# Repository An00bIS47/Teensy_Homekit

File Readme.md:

# Homekit

This project uses [platformio](https://platformio.org) as build tool. 

In the root directory of the project is a file named `platformio.ini` where you can define building environments, dependent libraries, add flags for compiling etc.

The `platformio.ini` consists of multiple environments (boards or build configurations) and uses additional scripts for modifying parameters for building depending on the users choices.

In short the command to build and upload this would be:

`pio run -e teensy_41 -t upload` 

or

`pio run -e teensy_41_debug -t upload` 

depending on the enviroment you want to build. Leave out `-t upload` for compiling only.

## plugins option:
```
[plugins]
bme280 = 1
led = 1
dht = 0
hygrometer = 0
knx = 0
```

With this option you can choose, which plugin should be available and enabled for your build. You can select multiple.
A `extra_script` will add the required source files to the `src_filter` and will also add the required defines and include paths.

## custom_options:

For each environment you will find the `custom_options`. There you can define, which feature options should be available. 

```
custom_options =
    teensy_debug = 0
    teensy_config_spiffs_ext = 0
    teensy_config_spiffs_int = 0
    config_eeprom = 1
    qrcode = 1
    ntp = 1
    webserver = 0
    ota_update = 0
    keystore = 0
    reset = 1
    wifi = 0
```

For the Teensy, only `teensy_debug`, `config_eeprom`, `ntp`, `qr_code` and `reset` will be working right now.

### teensy_debug
This will enable TeensyDebug

### config_eeprom
Use EEPROM to save the configuration and pairings

### ntp
Enables NTP as Time source

### reset
This will reset and delete the configuration from EEPROM.

### qr_code
This will enable a QR code generation and will print the QR code for pairing to Serial

## extra_scripts:

The scripts are located in the `scripts/platformio` folder and are referenced in the platformio.ini under 

```
[common]
extra_scripts =
	pre:scripts/platformio/pre_increment_version.py
	pre:scripts/platformio/pre_config_builder.py
	pre:scripts/platformio/pre_debug_macro.py
	;post:scripts/platformio/post_custom_debug_flags.py
	post:scripts/platformio/post_upload_delay.py
        scripts/platformio/custom_targets.py
```

The scripts do the following:
* `pre:scripts/platformio/pre_increment_version.py`:
 Increments the build number in the file `HAPBuildnumber` and adds infos about the git repository to `HAPVersionHomekit`
* `pre:scripts/platformio/pre_config_builder.py`: 
 Adds build flags (in particular: src_filter and build_flags) depending on the choices of the field `custom_options` for each environment. Additional it adds the same build flags for each "selected" plugin
* `pre:scripts/platformio/pre_debug_macro.py`: 
  Basically just adds the define `DEBUG=1` if the `release_type` is `debug`
* `post:scripts/platformio/post_custom_debug_flags.py`:
  This would change the `-0g`optimization parameter (which adds platformio as default if the `release_type` is set to `debug`) to `-0s`. Currently this is commented out
* `post:scripts/platformio/post_upload_delay.py`: 
  Adds a small delay of a few seconds after compiling so that the serial monitor can find the Teensy on the USB port.
* `scripts/platformio/custom_targets.py`: 
  Adds additional targets to the `pio run` command, like `teensy_size`, `tycmd reset` and so on.

I have not tested the scripts with Windows, but they should work on macOS and Linux.

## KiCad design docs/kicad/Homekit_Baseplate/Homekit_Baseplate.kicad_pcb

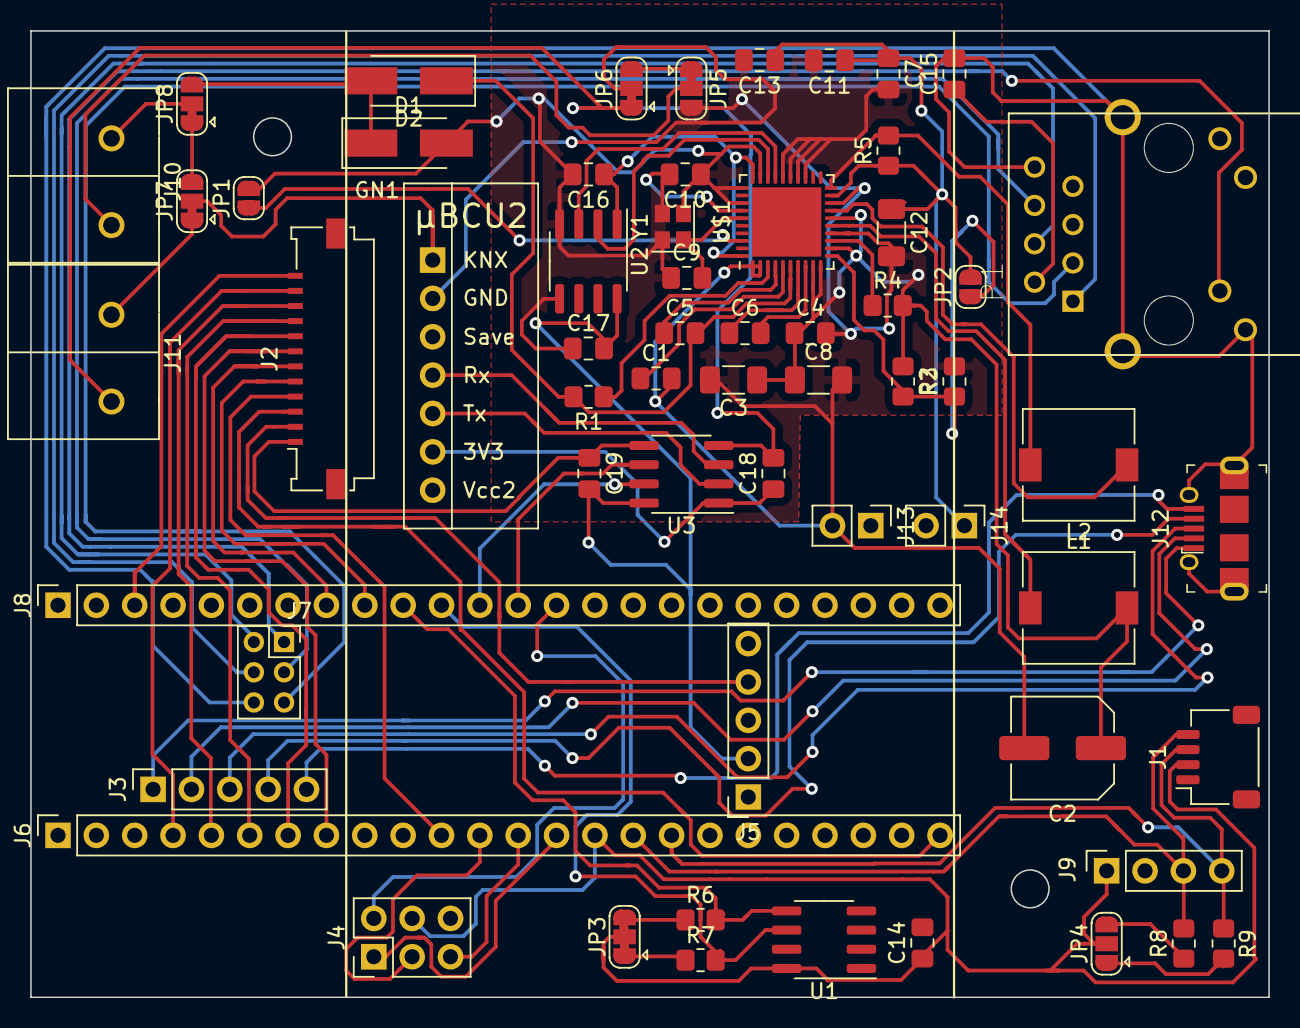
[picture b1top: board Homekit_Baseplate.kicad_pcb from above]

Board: 2 copper layers, 82.0 x 64.0 mm, 61 parts (0 on the bottom side), 68 nets.

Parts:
C1: 100nF / 50V; C_0805_2012Metric_Pad1.18x1.45mm_HandSolder
C2: 100µF / 35V; C_Elec_6.3x7.7
C3: 1µF / 50V; C_1206_3216Metric_Pad1.33x1.80mm_HandSolder
C4, C11: 10µF / 6.3V; C_0805_2012Metric_Pad1.18x1.45mm_HandSolder
C5: 47nF / 50V; C_0805_2012Metric_Pad1.18x1.45mm_HandSolder
C6: 47nF / 25V; C_0805_2012Metric_Pad1.18x1.45mm_HandSolder
C7, C13, C16, C17, C18, C19: 100nF / 6.3V; C_0805_2012Metric_Pad1.18x1.45mm_HandSolder
C8, C12: 10µF / 6.3V; C_1206_3216Metric_Pad1.33x1.80mm_HandSolder
C9, C10: 9pF / 6.3V; C_0805_2012Metric_Pad1.18x1.45mm_HandSolder
C14: 0.1µF / 6.3V; C_0805_2012Metric_Pad1.18x1.45mm_HandSolder
C15: 0.1µF / 50V; C_0805_2012Metric_Pad1.18x1.45mm_HandSolder
D1: TVS SMA40; D_SMA_Handsoldering
D2: D1; D_SMA_Handsoldering
GN1: Konnekting_µBCU; MicroBCU2_Solderd_Vertical
J1: J I2C/Serial QWIIC; JST_SH_SM04B-SRSS-TB_1x04-1MP_P1.00mm_Horizontal
J2: J Faceplate Connector; Molex_200528-0120_1x12-1MP_P1.00mm_Horizontal
J3: Teensy 4.1 USB; PinSocket_1x05_P2.54mm_Vertical
J4: SPI Breakout; PinHeader_2x03_P2.54mm_Vertical
J5: Teensy 4.1 Extra; PinSocket_1x05_P2.54mm_Vertical
J6: Teensy 4.1 Left; PinSocket_1x24_P2.54mm_Vertical
J7: Teensy 4.1 Ethernet Breakout; PinSocket_2x03_P2.00mm_Vertical
J8: Teensy 4.1 Right; PinSocket_1x24_P2.54mm_Vertical
J9: J I2C/Serial; PinSocket_1x04_P2.54mm_Vertical
J10, J11: Wago_243-211; WAGO 243-211 KNX
J12: Micro USB; USB_Micro_AB_Female_0475890001
J13, J14: 5V KNX Out; PinHeader_1x02_P2.54mm_Vertical
JP1: SJ HIGH POWER; SolderJumper-2_P1.3mm_Open_RoundedPad1.0x1.5mm
JP2: SJ 3V3 ONLY; SolderJumper-2_P1.3mm_Open_RoundedPad1.0x1.5mm
JP3: SJ ATECC608A PULLUPS; SolderJumper-3_P1.3mm_Bridged123_RoundedPad1.0x1.5mm
JP4: SJ QWIIC PULLUPS; SolderJumper-3_P1.3mm_Open_RoundedPad1.0x1.5mm
JP5, JP6, JP7, JP8: JUMPER-SMT_3_1-NC; SolderJumper-3_P1.3mm_Bridged12_RoundedPad1.0x1.5mm
L1, L2: 220µH; L_7.3x7.3_H4.5
P1: J1B1211CCD
R1: 22R; R_0805_2012Metric_Pad1.20x1.40mm_HandSolder
R2: 33k; R_0805_2012Metric_Pad1.20x1.40mm_HandSolder
R3: 180k; R_0805_2012Metric_Pad1.20x1.40mm_HandSolder
R4, R5: 1R; R_0805_2012Metric_Pad1.20x1.40mm_HandSolder
R6, R7, R8, R9: 4k7; R_0805_2012Metric_Pad1.20x1.40mm_HandSolder
U1: ATECC608A; SOIC-8_3.9x4.9mm_P1.27mm
U2, U3: ADuM1201AR; SOIC-8_3.9x4.9mm_P1.27mm
U$1: NCN5120; QFN-40-1EP_6x6mm_P0.5mm_EP4.6x4.6mm
Y1: 16MHz; Crystal_SMD_2520-4Pin_2.5x2.0mm

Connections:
+3V3: C14.1, C17.2, C19.2, J1.2, J2.12, J4.4, J5.2, J6.15, J8.3, J9.1, JP3.2, JP4.2, U1.8, U2.8, U3.8
+5V: J3.1, J8.1, J12.1
/CS_0: J4.3, J6.12
/Homekit_KNX/3V3_KNX_2: C18.1, GN1.6, U3.1
/Homekit_KNX/KNX+: J10.1, JP8.2
/Homekit_KNX/KNX-: J10.2, JP5.2
/Homekit_KNX/KNX_2+: J11.1, JP7.1
/Homekit_KNX/KNX_2-: C18.2, J11.2, JP6.1, U3.4
/Homekit_KNX/RX_1_KNX: U2.3, U$1.27
/Homekit_KNX/RX_2_KNX_2: GN1.4, U3.3
/Homekit_KNX/TX_1_KNX: U2.2, U$1.28
/Homekit_KNX/TX_2_KNX_2: GN1.5, U3.2
/LED_CONN: J2.9, J6.6
/LED_ERROR: J2.8, J6.7
/LED_ON: J2.11, J6.4
/LED_PROG: J2.10, J6.5
/LED_T41_PROG: J2.7, J6.8
/MISO_0: J4.1, J6.14
/MOSI_0: J4.5, J6.13
/PUSH_PROG: J2.4, J6.11
/PUSH_RESET: J2.3, J6.24
/PUSH_T41_PROG: J2.2, J5.4
/RX_1: J6.2, U2.7
/RX_3: J8.12, U3.7
/SCK_0: J4.2, J8.14
/SCL_0: J2.6, J8.8
/SCL_1: J8.11, R7.2, U1.6
/SCL_2_TX_6: J1.4, J6.16, J9.3, R8.2
/SDA_0: J2.5, J8.9
/SDA_1: J8.10, R6.2, U1.5
/SDA_2_RX_6: J1.3, J6.17, J9.4, R9.2
/TX_1: J6.3, U2.6
/TX_3: J8.13, U3.6
GND: C14.2, C15.2, C17.1, C19.1, J1.1, J2.1, J3.4, J3.5, J4.6, J5.3, J6.1, J7.5, J8.2, J8.15, J9.2, J12.4, J12.5, J12.SH, P1.8, P1.9, P1.13, P1.14, U1.4, U2.5, U3.5
GND1: C1.2, C2.2, C3.2, C4.2, C7.2, C8.2, C9.1, C10.1, C11.2, C12.2, C13.2, C16.2, D1.2, J13.2, J14.2, JP1.2, JP5.3, R3.2, U2.4, U$1.1, U$1.2, U$1.14, U$1.18, U$1.23, U$1.24, U$1.25, U$1.26, U$1.29, U$1.31, U$1.33, Y1.2, Y1.4
unnamed: C1.1, U$1.5
unnamed: C5.1, U$1.4
unnamed: C5.2, D2.1, R1.2, U$1.6
unnamed: C6.1, U$1.7
unnamed: C6.2, U$1.8
unnamed: C9.2, U$1.35, Y1.1
unnamed: C10.2, U$1.34, Y1.3
unnamed: C15.1, P1.2
unnamed: D1.1, D2.2, JP8.3
unnamed: GN1.1, JP7.2
unnamed: GN1.2, JP6.2
unnamed: J7.1, P1.4
unnamed: J7.2, P1.10
unnamed: J7.3, P1.1
unnamed: J7.4, P1.6
unnamed: J7.6, P1.3
unnamed: J3.2, J12.2
unnamed: J3.3, J12.3
unnamed: JP1.1, U$1.38
unnamed: JP2.1, R2.2, R3.1, U$1.11
unnamed: JP3.1, R7.1
unnamed: JP3.3, R6.1
unnamed: JP4.1, R9.1
unnamed: JP4.3, R8.1
unnamed: JP5.1, JP6.3
unnamed: JP7.3, JP8.1
unnamed: L1.1, U$1.15
unnamed: L2.1, U$1.17
unnamed: L2.2, R5.2, U$1.20
unnamed: R1.1, U$1.3
unnamed: R4.1, U$1.13
VCC_1: C7.1, C11.1, C12.1, C13.1, C16.1, J14.1, JP2.2, R5.1, U2.1, U$1.19, U$1.30, U$1.40
VCC_2: C2.1, C3.1, C4.1, C8.1, J13.1, L1.2, R2.1, R4.2, U$1.9, U$1.10, U$1.12, U$1.16

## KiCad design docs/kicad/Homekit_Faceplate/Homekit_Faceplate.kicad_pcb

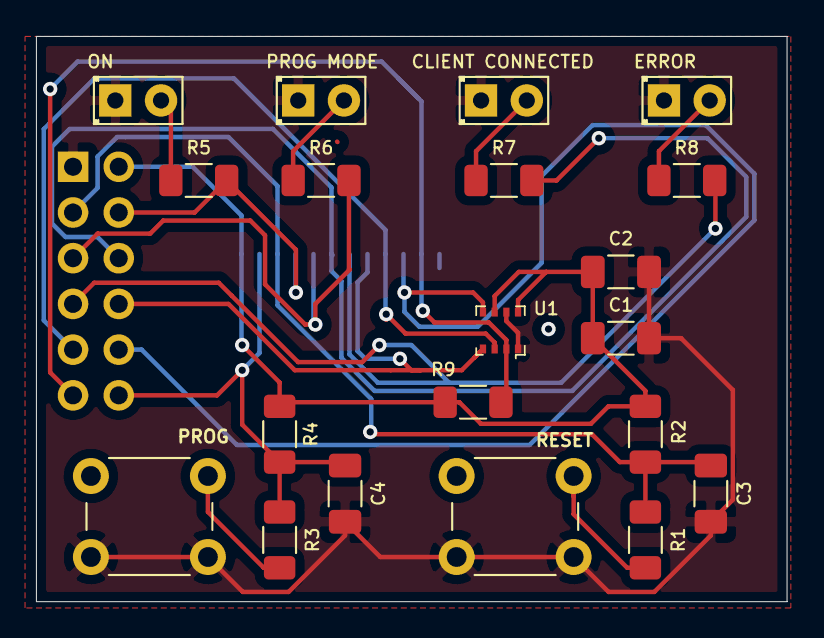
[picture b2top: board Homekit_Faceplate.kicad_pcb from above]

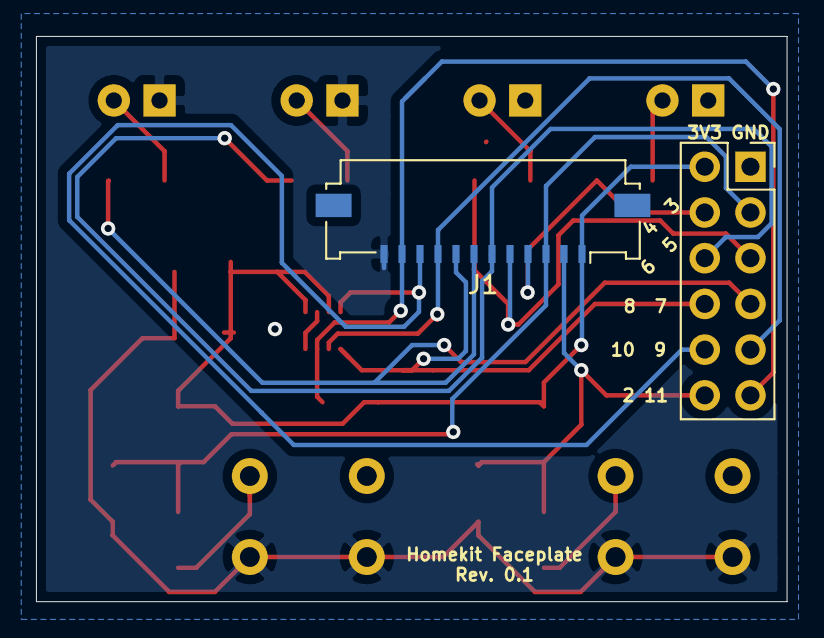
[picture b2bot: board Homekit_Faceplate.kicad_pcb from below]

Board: 2 copper layers, 41.7 x 31.4 mm, 22 parts (2 on the bottom side), 18 nets.

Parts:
C1, C2: 100nF; C_1206_3216Metric_Pad1.33x1.80mm_HandSolder
C3, C4: 0.1µF; C_1206_3216Metric_Pad1.33x1.80mm_HandSolder
D1: LED GREEN; LED_D2.0mm_W4.8mm_H2.5mm_FlatTop
D2, D4: LED RED; LED_D2.0mm_W4.8mm_H2.5mm_FlatTop
D3: LED ORANGE; LED_D2.0mm_W4.8mm_H2.5mm_FlatTop
J1: Conn_01x12; Molex_200528-0120_1x12-1MP_P1.00mm_Horizontal
J2: Conn_02x06_Odd_Even; PinSocket_2x06_P2.54mm_Vertical
R1, R3: 1k; R_1206_3216Metric_Pad1.30x1.75mm_HandSolder
R2, R4: 10k; R_1206_3216Metric_Pad1.30x1.75mm_HandSolder
R5, R6, R7, R8: 220R; R_1206_3216Metric_Pad1.30x1.75mm_HandSolder
R9: 4k7; R_1206_3216Metric_Pad1.30x1.75mm_HandSolder
SW1: PROG MODE; SW_PUSH_6mm
SW2: RESET; SW_PUSH_6mm
U1: BME280; Pressure_Sensor_LGA-8_2.5x2.5mm_BME280

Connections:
+3V3: C1.1, C2.1, J1.1, J2.2, R2.2, R4.2, R9.1, U1.6, U1.8
/2: C4.1, J1.2, J2.12, R3.1, R4.1
/3: C3.1, J1.3, J2.3, R1.1, R2.1
/4: J1.4, J2.4, R5.2
/5: J1.5, J2.5, R6.2
/6: J1.6, J2.6, R7.2
/7: J1.7, J2.7, R8.2
/8: J1.8, J2.8, U1.4
/9: J1.9, J2.9, U1.3
/10: J1.10, J2.10, U1.5
/11: J1.11, J2.11, R9.2, U1.2
GND: C1.2, C2.2, C3.2, C4.2, D1.1, D2.1, D3.1, D4.1, J1.12, J2.1, SW1.1, SW2.1, U1.1, U1.7
unnamed: D1.2, R5.1
unnamed: D2.2, R6.1
unnamed: D3.2, R7.1
unnamed: D4.2, R8.1
unnamed: R1.2, SW2.2
unnamed: R3.2, SW1.2

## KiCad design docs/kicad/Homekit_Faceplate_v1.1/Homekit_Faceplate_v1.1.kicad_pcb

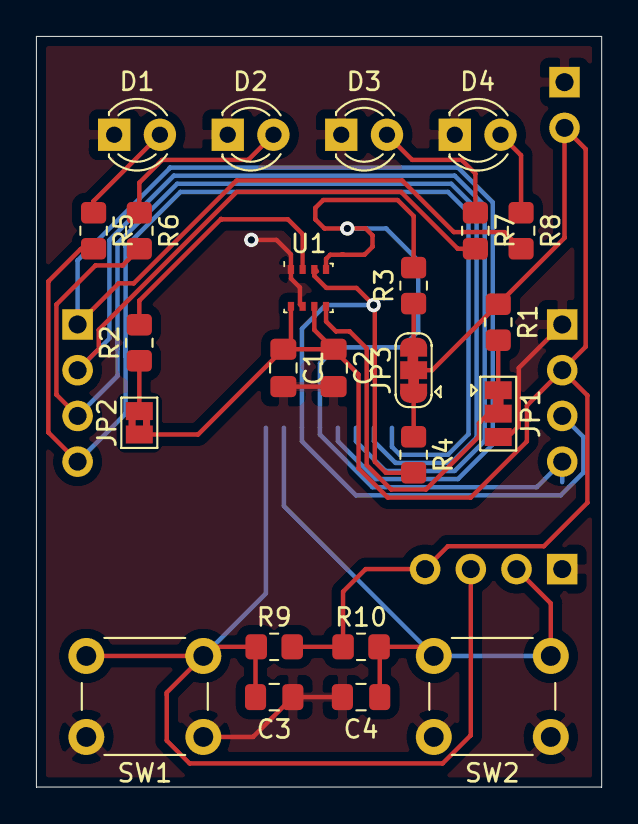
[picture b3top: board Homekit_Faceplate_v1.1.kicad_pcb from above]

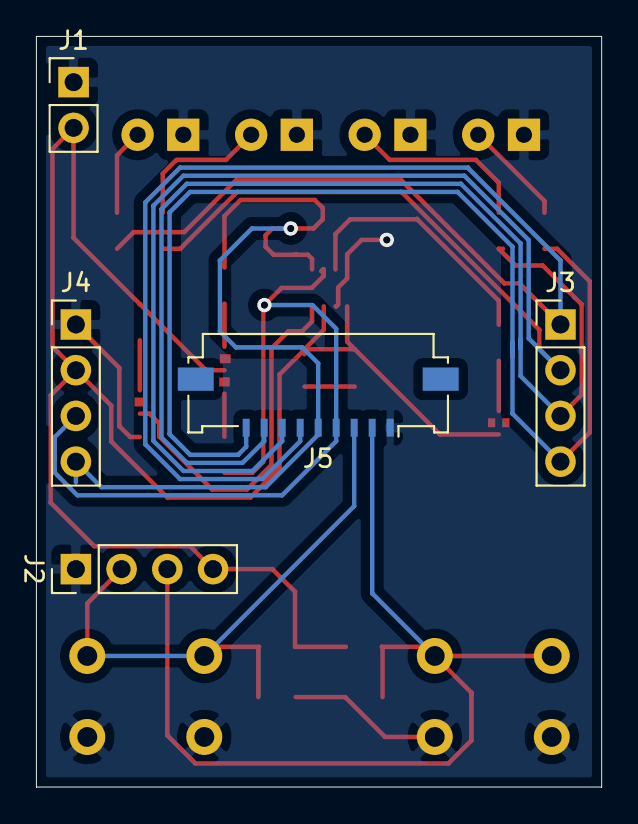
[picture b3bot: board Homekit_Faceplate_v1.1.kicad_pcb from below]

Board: 2 copper layers, 31.4 x 41.7 mm, 29 parts (5 on the bottom side), 20 nets.

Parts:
C1, C2, C3, C4: 0.1µF; C_0805_2012Metric_Pad1.18x1.45mm_HandSolder
D1: LED GREEN; LED_D3.0mm
D2, D4: LED RED; LED_D3.0mm
D3: LED ORANGE; LED_D3.0mm
J1: J Power; PinHeader_1x02_P2.54mm_Vertical
J2: J Push Buttons; PinHeader_1x04_P2.54mm_Vertical
J3: J Status LEDs; PinHeader_1x04_P2.54mm_Vertical
J4: J I2C; PinHeader_1x04_P2.54mm_Vertical
J5: J Flex Jumper to Teensy; Molex_200528-0090_1x09-1MP_P1.00mm_Horizontal
JP1: EN ADR PULLUP; SolderJumper-3_P1.3mm_Bridged12_Pad1.0x1.5mm
JP2: EN I2C MODE; SolderJumper-2_P1.3mm_Bridged2Bar_Pad1.0x1.5mm
JP3: EN I2C PULLUP; SolderJumper-3_P1.3mm_Bridged123_RoundedPad1.0x1.5mm
R1, R2, R3, R4: 4k7; R_0805_2012Metric_Pad1.20x1.40mm_HandSolder
R5, R6, R7, R8: 220R; R_0805_2012Metric_Pad1.20x1.40mm_HandSolder
R9, R10: 1k; R_0805_2012Metric_Pad1.20x1.40mm_HandSolder
SW1: SW PROG MODE; SW_PUSH_6mm
SW2: SW RESET; SW_PUSH_6mm
U1: BME280; Bosch_LGA-8_2.5x2.5mm_P0.65mm_ClockwisePinNumbering

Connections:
+3V3: C1.1, C2.1, J1.2, J2.4, J4.2, JP2.1, JP3.2, R1.1, R9.1, R10.1, U1.6, U1.8
/3: J3.4, J5.9, R5.2
/6: J3.3, J5.8, R6.2
/9: J3.2, J5.7, R7.2
/11: J3.1, J5.6, R8.2
/PB1: C3.1, J2.3, J5.2, R9.2, SW1.2
/PB2: C4.1, J2.2, J5.3, R10.2, SW2.2
/SCL: J4.4, J5.5, R3.2, U1.4
/SDA: J4.3, J5.4, R4.2, U1.3
GND: C1.2, C2.2, C3.2, C4.2, D1.1, D2.1, D3.1, D4.1, J1.1, J2.1, J4.1, J5.1, JP1.3, SW1.1, SW2.1, U1.1, U1.7
unnamed: D1.2, R5.1
unnamed: D2.2, R6.1
unnamed: D3.2, R7.1
unnamed: D4.2, R8.1
unnamed: JP1.1, R1.2
unnamed: JP1.2, U1.5
unnamed: JP2.2, R2.1
unnamed: JP3.1, R4.1
unnamed: JP3.3, R3.1
unnamed: R2.2, U1.2

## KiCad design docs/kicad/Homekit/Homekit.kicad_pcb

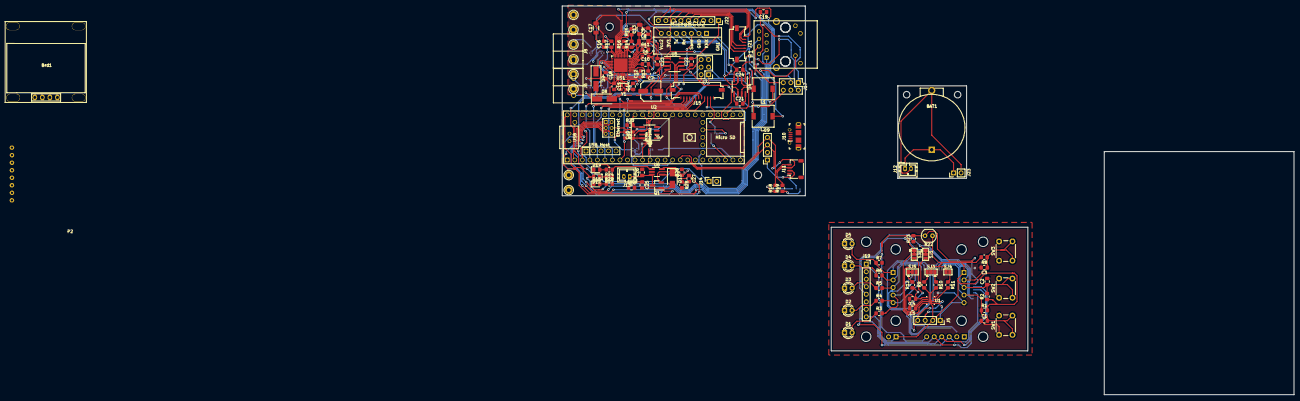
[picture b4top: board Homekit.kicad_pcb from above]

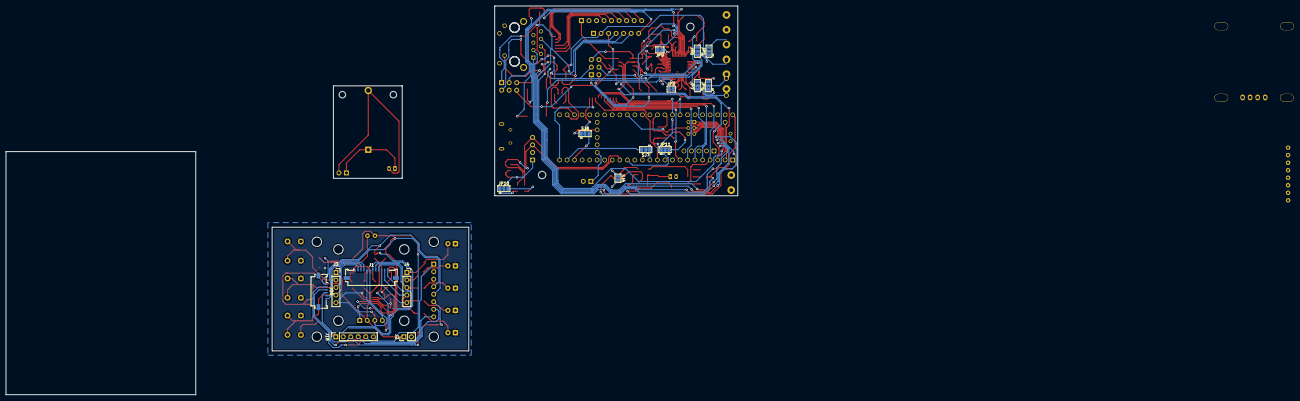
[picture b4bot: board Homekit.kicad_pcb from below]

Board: 2 copper layers, 246.8 x 131.1 mm, 124 parts (17 on the bottom side), 102 nets.

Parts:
BAT1: RTC Battery; Battery_Holder_Coin_2032_BS-7
Brd1: SSD1306; 128x64OLED
C1, C2, C3, C4, C5: 0.1µF; C_0805_2012Metric_Pad1.18x1.45mm_HandSolder
C6: 100nF / 50V; C_0805_2012Metric_Pad1.18x1.45mm_HandSolder
C7: 100µF / 35V; C_Elec_6.3x7.7
C8: 1µF / 50V; C_1206_3216Metric_Pad1.33x1.80mm_HandSolder
C9, C16: 10µF / 6.3V; C_0805_2012Metric_Pad1.18x1.45mm_HandSolder
C10: 47nF / 50V; C_0805_2012Metric_Pad1.18x1.45mm_HandSolder
C11: 47nF / 25V; C_0805_2012Metric_Pad1.18x1.45mm_HandSolder
C12, C18, C21, C22, C23, C24: 100nF / 6.3V; C_0805_2012Metric_Pad1.18x1.45mm_HandSolder
C13, C17: 10µF / 6.3V; C_1206_3216Metric_Pad1.33x1.80mm_HandSolder
C14, C15: 9pF / 6.3V; C_0805_2012Metric_Pad1.18x1.45mm_HandSolder
C19: 0.1µF / 50V; C_0805_2012Metric_Pad1.18x1.45mm_HandSolder
C20: 0.1µF / 6.3V; C_0805_2012Metric_Pad1.18x1.45mm_HandSolder
C25, C26: 4.7µF / 6.3 V; C_0805_2012Metric_Pad1.18x1.45mm_HandSolder
C27: 1µF / 6.3 V; C_0805_2012Metric_Pad1.18x1.45mm_HandSolder
D1: LED GREEN; LED_D3.0mm
D2, D4, D5: LED RED; LED_D3.0mm
D3: LED ORANGE; LED_D3.0mm
D8: TVS SMA40; D_SMA_Handsoldering
D9: D1; D_SMA_Handsoldering
D12: LED Red; LED_0805_2012Metric_Pad1.15x1.40mm_HandSolder
D13: B130-E3; D_SMA
D14: LED Green; LED_0805_2012Metric_Pad1.15x1.40mm_HandSolder
D15: LED RED; LED_0805_2012Metric_Pad1.15x1.40mm_HandSolder
GN1: Konnekting_µBCU; MicroBCU2_Solderd_Vertical
J1, J15: J Faceplate Connector; Molex_200528-0120_1x12-1MP_P1.00mm_Horizontal
J2: J Power; PinHeader_1x02_P2.54mm_Vertical
J3: J Push Buttons; PinSocket_1x05_P2.54mm_Vertical
J4: J Status LEDs; PinSocket_1x05_P2.54mm_Vertical
J5: J Display SSD1306; PinSocket_1x04_P2.54mm_Vertical
J6, J8: Wago_243-211; WAGO 243-211 KNX
J7: J KNX1 Breakout; PinHeader_2x03_P2.54mm_Vertical
J9: J I2C/Serial; PinSocket_1x04_P2.54mm_Vertical
J10: Micro USB; USB_Micro_AB_Female_0475890001
J11: J I2C/Serial QWIIC; JST_SH_SM04B-SRSS-TB_1x04-1MP_P1.00mm_Horizontal
J12: J RTC BatteryPack; JST_PH_B2B-PH-K_1x02_P2.00mm_Vertical
J13: JST Battery; JST_PH_B2B-PH-K_1x02_P2.00mm_Vertical
J14: J RTC Battery Socket; PinSocket_1x02_P2.54mm_Vertical
J17: J KNX2 Breakout; PinHeader_2x03_P2.54mm_Vertical
J18: J Breakout SPI; PinSocket_1x06_P2.54mm_Vertical
J19: J Display SSD1327; PinSocket_1x08_P2.54mm_Vertical
J20: J Connector SPI; Molex_200528-0060_1x06-1MP_P1.00mm_Horizontal
J21: J Connector SPI+; Molex_200528-0060_1x06-1MP_P1.00mm_Horizontal
J22: J SPI Display Breakout; PinSocket_1x09_P2.54mm_Vertical
J23: J RTC Breakout; PinHeader_1x02_P2.54mm_Vertical
JP4: SJ KNX1 GND; SolderJumper-3_P1.3mm_Bridged2Bar12_Pad1.0x1.5mm
JP5: SJ KNX2 GND; SolderJumper-3_P1.3mm_Bridged2Bar12_Pad1.0x1.5mm
JP6: SJ KNX2+; SolderJumper-3_P1.3mm_Bridged2Bar12_Pad1.0x1.5mm
JP7: SJ KNX1+; SolderJumper-3_P1.3mm_Bridged2Bar12_Pad1.0x1.5mm
JP8: SJ HIGH POWER; SolderJumper-2_P1.3mm_Open_Pad1.0x1.5mm
JP9: SJ 3V3 ONLY; SolderJumper-2_P1.3mm_Open_Pad1.0x1.5mm
JP10: SJ QWIIC PULLUPS; SolderJumper-3_P1.3mm_Open_Pad1.0x1.5mm
JP11: SJ ATECC608A PULLUPS; SolderJumper-3_P1.3mm_Bridged2Bar123_Pad1.0x1.5mm
L1, L2: 220µH; L_7.3x7.3_H4.5
P1: J1B1211CCD
P2: SSD1327; Waveshare_OLED_SSD1327_128x128
Q1: DMP1045U; SOT-23_Handsoldering
R1, R2, R8: 1k; R_0805_2012Metric_Pad1.20x1.40mm_HandSolder
R3, R4, R5, R6, R7, R29: 220R; R_0805_2012Metric_Pad1.20x1.40mm_HandSolder
R9, R10, R11, R12, R18, R19, R20, R21: 4k7; R_0805_2012Metric_Pad1.20x1.40mm_HandSolder
R13: 22R; R_0805_2012Metric_Pad1.20x1.40mm_HandSolder
R14: 33k; R_0805_2012Metric_Pad1.20x1.40mm_HandSolder
R15: 180k; R_0805_2012Metric_Pad1.20x1.40mm_HandSolder
R16, R17: 1R; R_0805_2012Metric_Pad1.20x1.40mm_HandSolder
R22: R_PHOTO; R_LDR_4.9x4.2mm_P2.54mm_Vertical
R23, R25: 10k; R_0805_2012Metric_Pad1.20x1.40mm_HandSolder
R24, R27: 470R; R_0805_2012Metric_Pad1.20x1.40mm_HandSolder
R26: 100k; R_0805_2012Metric_Pad1.20x1.40mm_HandSolder
R28: 2k5; R_0805_2012Metric_Pad1.20x1.40mm_HandSolder
SJ1, SJ2: SolderJumper_3_Bridged12; SolderJumper-3_P1.3mm_Bridged12_Pad1.0x1.5mm
SJ3: EN I2C PULLUP; SolderJumper-3_P1.3mm_Bridged2Bar123_Pad1.0x1.5mm
SJ4: EN I2C MODE; SolderJumper-2_P1.3mm_Bridged2Bar_Pad1.0x1.5mm
SJ5: EN ADR PULLUP; SolderJumper-3_P1.3mm_Bridged12_Pad1.0x1.5mm
SJ6: SolderJumper_2_Open; SolderJumper-2_P1.3mm_Open_Pad1.0x1.5mm
SJ7: SJ SPI CS Select; SolderJumper-3_P1.3mm_Bridged12_Pad1.0x1.5mm
SJ8: SJ PUSH RES; SolderJumper-3_P1.3mm_Bridged12_Pad1.0x1.5mm
SW1: SW T41 PROG MODE; SW_PUSH_6mm
SW2: SW RESET; SW_PUSH_6mm
SW3: SW PROG MODE; SW_PUSH_6mm
U1: BME280; Bosch_LGA-8_2.5x2.5mm_P0.65mm_ClockwisePinNumbering
U2: Teensy4.1; Teensy41
U3: ATECC608A; SOIC-8_3.9x4.9mm_P1.27mm
U4, U5: ADuM1201AR; SOIC-8_3.9x4.9mm_P1.27mm
U6: MCP73832; TSOT-23-5_HandSoldering
US1: NCN5120; QFN-40-1EP_6x6mm_P0.5mm_EP4.6x4.6mm
Y1: 16MHz; Crystal_SMD_2520-4Pin_2.5x2.0mm

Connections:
+3V3: C4.1, C5.1, C20.1, C21.2, C22.2, J1.12, J2.1, J3.1, J5.2, J9.1, J11.2, J15.12, J19.1, J22.1, JP10.2, JP11.2, R1.1, R2.1, R8.1, R12.1, R22.1, SJ3.2, SJ4.1, U1.6, U1.8, U2.15, U2.46, U3.8, U4.8, U5.8
/Homekit_Battery.sch/VBAT: BAT1.Pos, J12.2, J23.2
/Homekit_Battery.sch/VIN: C27.1, D13.1, Q1.2, U2.49
/Homekit_Battery.sch/VUSB: C25.1, D12.2, D13.2, Q1.1, R26.1, U2.48, U6.4
/Homekit_Faceplate/CS: J18.3, J19.6, J20.4, J21.4, J22.6, SJ7.1
/Homekit_Faceplate/DC: J18.4, J19.7, J20.3, J21.3, J22.7, U2.14
/Homekit_Faceplate/LDR: J18.6, J20.1, J21.1, J22.9, R22.2, R23.2, U2.32
/Homekit_Faceplate/LED_CONN: J1.9, J4.3, J15.9, R5.2, U2.6
/Homekit_Faceplate/LED_ERROR: J1.8, J4.2, J15.8, R6.2, U2.7
/Homekit_Faceplate/LED_ON: J1.10, J4.5, J15.10, R4.2, U2.5
/Homekit_Faceplate/LED_PROG: J1.11, J4.4, J15.11, R3.2, R29.2, U2.4
/Homekit_Faceplate/LED_T41_PROG: J1.7, J4.1, J15.7, R7.2, U2.8
/Homekit_Faceplate/MOSI: J19.4, J20.6, J21.6, J22.4, SJ2.1, U2.13
/Homekit_Faceplate/PUSH_PROG: C3.1, J1.4, J3.2, J15.4, R8.2, SW3.2, U2.11
/Homekit_Faceplate/PUSH_RESET: C2.1, J1.3, J3.3, J15.3, R2.2, SW2.2, U2.24
/Homekit_Faceplate/PUSH_T41_PROG: C1.1, J1.2, J3.4, J15.2, R1.2, SJ8.1, SJ8.2, SW1.2, U2.53
/Homekit_Faceplate/RST: J18.5, J19.8, J20.2, J21.2, J22.8, U2.33
/Homekit_Faceplate/SCK: J19.5, J20.5, J21.5, J22.5, SJ1.1, U2.35
/Homekit_Faceplate/SCL: J5.3, R9.2, SJ1.3, U1.4
/Homekit_Faceplate/SCL0: J1.6, J15.6, U2.41
/Homekit_Faceplate/SDA0: J1.5, J5.4, J15.5, R10.2, SJ2.3, U1.3, U2.40
/Homekit_KNX/KNX1+: J6.2, JP7.2
/Homekit_KNX/KNX1-: J6.1, JP4.2
/Homekit_KNX/KNX1_RX: J7.2, U5.2, US1.27
/Homekit_KNX/KNX1_SAVE: J7.6, US1.36
/Homekit_KNX/KNX1_TX: J7.1, U5.3, US1.28
/Homekit_KNX/KNX2+: J8.2, JP6.3
/Homekit_KNX/KNX2-: J8.1, JP5.3
/Homekit_KNX/KNX2_3V3: C24.1, GN1.6, J17.5, U4.1
/Homekit_KNX/KNX2_5V: GN1.7, J17.3
/Homekit_KNX/KNX2_GND: C24.2, GN1.2, J17.4, JP5.2, U4.4
/Homekit_KNX/KNX2_RX: GN1.4, J17.2, U4.2
/Homekit_KNX/KNX2_SAVE: GN1.3, J17.6
/Homekit_KNX/KNX2_TX: GN1.5, J17.1, U4.3
/Homekit_Teensy/CS0: SJ7.2, U2.12
/Homekit_Teensy/CS1: SJ7.3, U2.23
/Homekit_Teensy/PUSH_RESERVED: SJ8.3, U2.22
/Homekit_Teensy/RX1: U2.2, U5.6
/Homekit_Teensy/RX8: U2.26, U4.6
/Homekit_Teensy/TX1: U2.3, U5.7
/Homekit_Teensy/TX8: U2.27, U4.7
/Homekit_Teensy/VBAT: J14.1, U2.50
GND: C1.2, C2.2, C3.2, C4.2, C5.2, C19.2, C20.2, C21.1, C22.1, C25.2, C26.2, C27.2, D1.1, D2.1, D3.1, D4.1, D5.1, D14.1, D15.1, J1.1, J2.2, J3.5, J5.1, J9.2, J10.4, J10.5, J10.SH, J11.1, J13.2, J14.2, J15.1, J19.2, J22.2, P1.8, P1.9, P1.13, P1.14, R23.1, R25.2, R26.2, R28.2, SJ5.3, SW1.1, SW2.1, SW3.1, U1.1, U1.7, U2.1, U2.34, U2.47, U2.52, U2.58, U2.59, U2.64, U3.4, U4.5, U5.5, U6.2
GND1: C6.2, C7.2, C8.2, C9.2, C12.2, C13.2, C14.1, C15.1, C16.2, C17.2, C18.2, C23.2, D8.2, J7.4, JP4.3, JP8.2, R15.2, U5.4, US1.1, US1.2, US1.14, US1.18, US1.23, US1.24, US1.25, US1.26, US1.29, US1.31, US1.33, Y1.2, Y1.4
unnamed: BAT1.Neg, J12.1, J23.1
unnamed: C6.1, US1.5
unnamed: C10.1, US1.4
unnamed: C10.2, D9.1, R13.2, US1.6
unnamed: C11.1, US1.7
unnamed: C11.2, US1.8
unnamed: C14.2, US1.35, Y1.1
unnamed: C15.2, US1.34, Y1.3
unnamed: C19.1, P1.2
unnamed: C26.1, J13.1, Q1.3, U6.3
unnamed: D1.2, R3.1
unnamed: D2.2, R4.1
unnamed: D3.2, R5.1
unnamed: D4.2, R6.1
unnamed: D5.2, R7.1
unnamed: D8.1, D9.2, JP7.3
unnamed: D12.1, R27.2
unnamed: D14.2, R24.2
unnamed: D15.2, R29.1
unnamed: GN1.1, JP6.2
unnamed: J10.1, U2.55
unnamed: J10.2, U2.56
unnamed: J10.3, U2.57
unnamed: J9.3, J11.3, R19.2, U2.17
unnamed: J9.4, J11.4, R18.2, U2.16
unnamed: J18.1, SJ2.2
unnamed: J18.2, SJ1.2
unnamed: JP4.1, JP5.1
unnamed: JP6.1, JP7.1
unnamed: JP8.1, US1.38
unnamed: JP9.1, R14.2, R15.1, US1.11
unnamed: JP10.1, R19.1
unnamed: JP10.3, R18.1
unnamed: JP11.1, R20.1
unnamed: JP11.3, R21.1
unnamed: L1.1, US1.15
unnamed: L2.1, US1.17
unnamed: L2.2, R17.2, US1.20
unnamed: P1.1, U2.63
unnamed: P1.3, U2.62
unnamed: P1.4, U2.60
unnamed: P1.6, U2.65
unnamed: P1.10, U2.61
unnamed: R9.1, SJ3.1
unnamed: R10.1, SJ3.3
unnamed: R11.1, SJ4.2
unnamed: R11.2, U1.2
unnamed: R12.2, SJ5.1
unnamed: R13.1, US1.3
unnamed: R16.1, US1.13
unnamed: R20.2, U2.39, U3.5
unnamed: R21.2, U2.38, U3.6
unnamed: R24.1, R27.1, U6.1
unnamed: R25.1, SJ6.1, U6.5
unnamed: R28.1, SJ6.2
unnamed: SJ5.2, U1.5
VCC_1: C12.1, C16.1, C17.1, C18.1, C23.1, J7.5, JP9.2, R17.1, U5.1, US1.19, US1.30, US1.40
VCC_2: C7.1, C8.1, C9.1, C13.1, J7.3, L1.2, R14.1, R16.2, US1.9, US1.10, US1.12, US1.16

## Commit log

2020-11-29 first working draft of homekit
2020-11-29 small fixes
2020-11-29 .gitignore is now working
2020-11-30 working get char und events
2020-11-30 working draft with ios14
2021-02-06 working draft
2021-02-06 removed inline
2021-02-06 fixed hapclient handling
2021-02-07 fixed fakegto
2021-02-16 removed unused mbedtls items from config.h
2021-02-18 added external flash support for homekit
2021-02-20 fixed float value for BME280
2021-02-21 added HAPCharacteristic STL
2021-02-27 small fixes and EEPROM rewrite
2021-02-28 some program size optimazation
2021-03-01 further optimized and compiling draft
2021-03-01 reduced filesize by moving functions to flash via flashmem
2021-03-01 reduced filesize
2021-03-07 draft of HAPTime
2021-03-23 added HAPTime and average fakegato for bme and weather
2021-03-27 started
2021-03-28 WIP: started on refactoring
2021-03-28 WIP: bit more progress
2021-03-28 maybe corrupted
2021-03-28 small changes
2021-03-28 commented out extmen/new
2021-03-29 updated knx lib
2021-03-29 WIP: more work
2021-03-29 WIP: even more work
2021-03-30 WIP: compiling works
2021-03-30 working sample and already remove old chars
2021-03-30 small cleanup
2021-03-30 WIP: started on HAPEventManager
2021-03-31 WIP: started on fakegato2
2021-04-01 WIP: compiling new fakegato
2021-04-01 WIP: trying sample
2021-04-02 added teensy_debug to launch.json
2021-04-02 fixed tlv and hapclient
2021-04-02 WIP: working except fakegato
2021-04-03 small fixes on fakegato
2021-04-03 WIP: Refactoring fakegato signature and value retrieval on going
2021-04-03 WIP: filesze of history entry seems not be corret
2021-04-04 WIP: fixed fakegato2 history entries
2021-04-04 Fakegato2 is working
2021-04-04 added utils and tester
2021-04-04 added readme's
2021-04-04 added teensy_debug option to launch.json
2021-04-05 WIP: Refactored some plugins for fakegato2
2021-04-06 WIP: compiling KNX with fakegato2
2021-04-06 removed old fakegato files
2021-04-06 added gitlab-ci.yml
2021-04-06 changed docker image to python:3-slim
2021-04-06 rename files
2021-04-06 added submodule knx locally hosted
2021-04-06 changed knx git type to ssh
2021-04-06 changed gitlab.yml
2021-04-09 small changes on gitlab and HAPEventManager
2021-04-09 removed lib/knx
2021-04-09 added knx as submodule
2021-04-09 changes knx to public url
2021-04-09 changed values yaml
2021-04-09 changed gitlab ci yaml
2021-04-09 added entropy.diff
2021-04-09 changed gitlab yml
2021-04-25 WIP: Updated tester
2021-04-25 WIP: Fakegato - made buffer size fixed to 512
2021-04-26 Fixed fakegato entrycounter and buffer overflow
2021-04-26 fixed fakegato signature
2021-04-26 WIP: fixed fakegato signature
2021-04-26 Fixed vtable error on Fakegato chars
2021-04-26 Bump buildnumber
2021-04-26 updated gitignore
2021-04-29 changed uploader protocol to cli
2021-04-29 fixed DHT serial output
2021-04-30 fixed buffer overflow when overwritting fakegato entry
2021-04-30 bump version
2021-04-30 removed trailing spaces
2021-05-01 reduced file size
2021-05-02 changed platformio.ini
2021-05-09 WIP: Small fixes on TLV8
2021-05-10 WIP: Added tests for tlv, srp and hash
2021-05-10 fixed c20p1305 decrypt
2021-05-12 Fixes on crypto
2021-05-12 small fixes on crypto
2021-05-12 Refactored HAPClient and added StreamUtils for buffer client read and HAPChunkedPrint for buffered client write
2021-05-12 tested
2021-05-12 small fixes on HAPSRP
2021-05-12 debug compiler config is working
2021-05-13 integrated gitlab upload to homekit_tester
2021-05-13 small fixes on tester
2021-05-13 refactored sending
2021-05-13 added pairings test methods
2021-05-14 small fixes2
2021-05-14 WIP: fix for verify error on M3
2021-05-14 WIP: fix for handleclientstate:
2021-05-14 WIP: fixed verify M3 problem
2021-05-14 fixed verify m3 bug
2021-05-14 WIP: playing with timeouts for hapclients in handle
2021-05-15 fixed memory leak @ hapclient disconnect
2021-05-15 small fixes on HAPTime
2021-05-15 fixed HAPTime begin
2021-05-16 rewrote send json doc
2021-05-17 FIX? HAPTime timestamp offset is 2* t_offset to high
2021-05-18 small fixes12
2021-05-18 Fixed fakegato
2021-05-18 removed mbedtls_base64 from HAPFakegato and HAPAccessorySet
2021-05-20 WIP: Refactored HAPFakegato+Schedule
2021-05-21 WIP: Started on fakegato schedule dst
2021-05-21 WIP: Tested tests and small fixes on fakegato
2021-05-21 WIP: Fakegato Schedule added DST
2021-05-21 Fix on Fakegato Reftime entries
2021-05-21 fixed fakegato reftime entries
2021-05-24 Tested successful
2021-05-24 small compiler fixes
2021-05-25 WIP: Removed knx from debug platformio config
2021-05-25 Commented out sending json docs unchunked
2021-05-26 WIP: Moved _curline to function
2021-05-26 WIP: added more strings to flashstring
2021-05-26 Added teensy_41_testing env to ini
2021-05-26 Working debug again :)
2021-05-28 Debug no longer working :(
2021-05-28 WIP: change string in request processing
2021-05-28 WIP: start
2021-05-28 WIP: replaced String with const char in request processing
2021-05-28 merged dev
2021-05-28 removed string from handleputchar
2021-05-28 merged dev-fix
2021-05-29 WIP: removed stopEvents and small fixes for no logging - BUT broke Debugging again :(
2021-05-29 tester: only save detailed steps if iterations <= 10
2021-05-29 tester: fixed faketo size 0?
2021-05-29 tester: fixed fakegato used == 0
2021-05-30 WIP: Added HAPChars. test and started on HAPChar...Data
2021-05-30 WIP: Rework fakegato for data chr
2021-05-30 added data chrs in fakegato schedule
2021-06-23 WIP: started on logging
2021-06-28 Changed Logging (not yet all complete) and HAPTime::timeString returns now a const char*
2021-06-28 merged with dev
2021-06-28 Removed value from HAPEvent
2021-06-28 broken...
2021-06-29 changed spiffs to eeprom for beta11 and small fixes
2021-06-30 updated libs
2021-06-30 changed request params to std::string
2021-07-02 Added access to elements in eventqueue
2021-07-02 WIP: test
2021-07-02 test
2021-07-02 Updated platformio ini
2021-07-03 Added platformio tasks and stuff
2021-07-03 updated platformio.ini
2021-07-03 added increment version to pio as target to extra_script.py
2021-07-04 small fixes on mdns advertising and logging
2021-07-04 WIP: BME280 removed String completely
2021-07-04 WIP: Version and Plugin Name -> breaks getAccessories
2021-07-04 WIP: version is now std::string
2021-07-05 HAPVersion changed to std::string
2021-07-05 WIP: changed firmware chr to std::string in HAPAccessory
2021-07-05 WIP: Changed HAPAccessory String chrs to std::string chrs
2021-07-05 WIP: removed string from HAPRequest and HAPService
2021-07-05 Added LOGARRAY_X and LOGMPI_X to HAPLogging
2021-07-05 Changed HAPBuildnumber date format to english
2021-07-06 Added HAPTime to HAPLogging
2021-07-08 Rewritten platformio.ini
2021-07-08 fixes
2021-07-10 WIP: Replaced Categories with HAPAccessoryType
2021-07-10 Replaced Services with HAPServiceType
2021-07-10 Replaced Characteristics with HAPCharacteristicType
2021-07-11 Fixed float chars and HAPTime
2021-07-12 Fixed Serialnumber
2021-07-12 Working in App again
2021-07-15 Small fixes on HAPTime and DEBUG off
2021-07-16 Removed FLASHMEM from Fakegato functions
2021-07-17 Cleaned up some files
2021-07-17 cleaned up
2021-07-17 cleanup
2021-07-19 Added additional Logging statements
2021-07-19 Added rolling_logger to utils
2021-07-20 Changed enums in Fakegato Schedule
2021-07-20 Reworked enums
2021-07-24 Reworked DeviceId
2021-07-24 fixed sign-compare warnings
2021-07-24 Added intervalTimer with a blinking LED for debug
2021-07-24 Fixed interupt handling in eventmanager
2021-07-25 changed subscribtion items to uint8 and uint32
2021-07-26 Added build instructions on Readme
